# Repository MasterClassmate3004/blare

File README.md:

# Blare

## Description

Blare is a custom alarm clock with 6 keys, a buzzer and a TFT display. It has 2 modes, a stopwatch mode and a normal clock mode. A stopwatch mode measures elapsed time from the moment you start it to the moment you stop it. A normal clock time measures the normal time which you can adjust with the 2 specified buttons.

## Features
- 6 mechanical keys
- A buzzer
- TFT Display
- Dual mode (Stopwatch/Clock)
- Adjustable Time

## Bills of Materials
- 1x Seeed XIAO RP2040
- 6x MX-Style Switches
- 6x White Blank DSA keycaps
- 6x through hole 1N4148 Diodes
- 1x 2.25in TFT Screen
- 1x 3.3V Piezo Buzzer
- 1x 2.54mm 8pin Male Header
- 8x 20cm Female-Female Jumper Wires
- 8x M2X5X4 Heatset Inserts
- Top Case 3D Print
- Bottom Case 3D Print

## Images

# PCB

# CAD

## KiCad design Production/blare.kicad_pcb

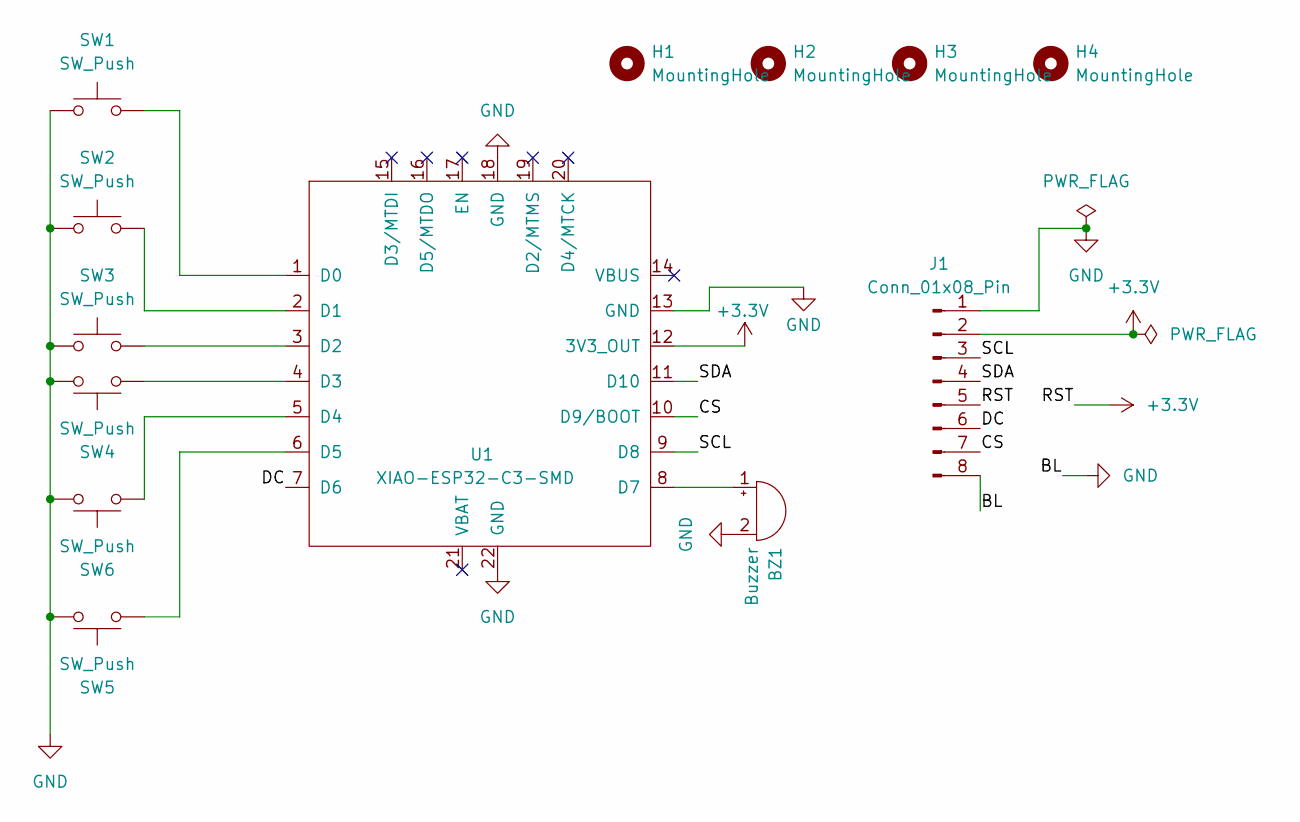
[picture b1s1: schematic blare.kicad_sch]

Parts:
BZ1: Buzzer; Buzzer_12x9.5RM7.6
H1, H2, H3, H4: MountingHole; MountingHole_3.2mm_M3
J1: Conn_01x08_Pin; PinSocket_1x08_P2.54mm_Vertical
SW1, SW2, SW3, SW4, SW5, SW6: SW_Push; SW_Cherry_MX_1.00u_PCB
U1: XIAO-ESP32-C3-SMD

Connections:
+3.3V: J1.2, J1.5, U1.12 (3V3_OUT)
/CS: J1.7, U1.10 (D9/BOOT)
/DC: J1.6, U1.7 (D6)
/SCL: J1.3, U1.9 (D8)
/SDA: J1.4, U1.11 (D10)
GND: BZ1.2 (-), J1.1, J1.8, SW1.1, SW2.1, SW3.1, SW4.2, SW5.2, SW6.2, U1.13 (GND), U1.18 (GND), U1.22 (GND)
unnamed: BZ1.1 (+), U1.8 (D7)
unnamed: SW1.2, U1.1 (D0)
unnamed: SW2.2, U1.2 (D1)
unnamed: SW3.2, U1.3 (D2)
unnamed: SW4.1, U1.4 (D3)
unnamed: SW6.1, U1.5 (D4)
unnamed: SW5.1, U1.6 (D5)

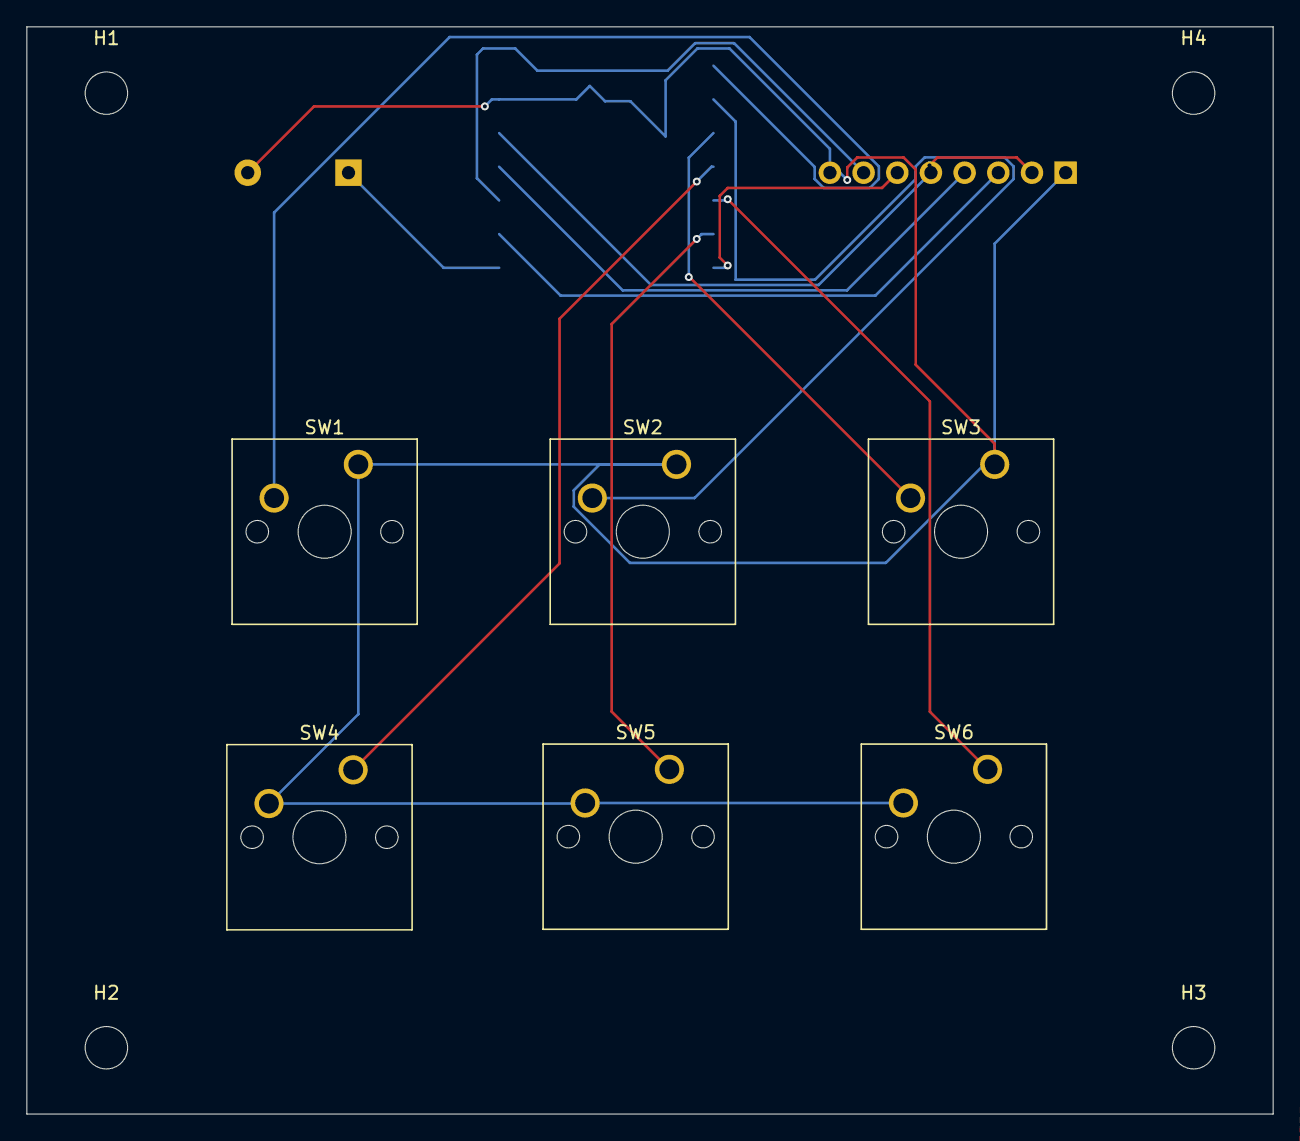
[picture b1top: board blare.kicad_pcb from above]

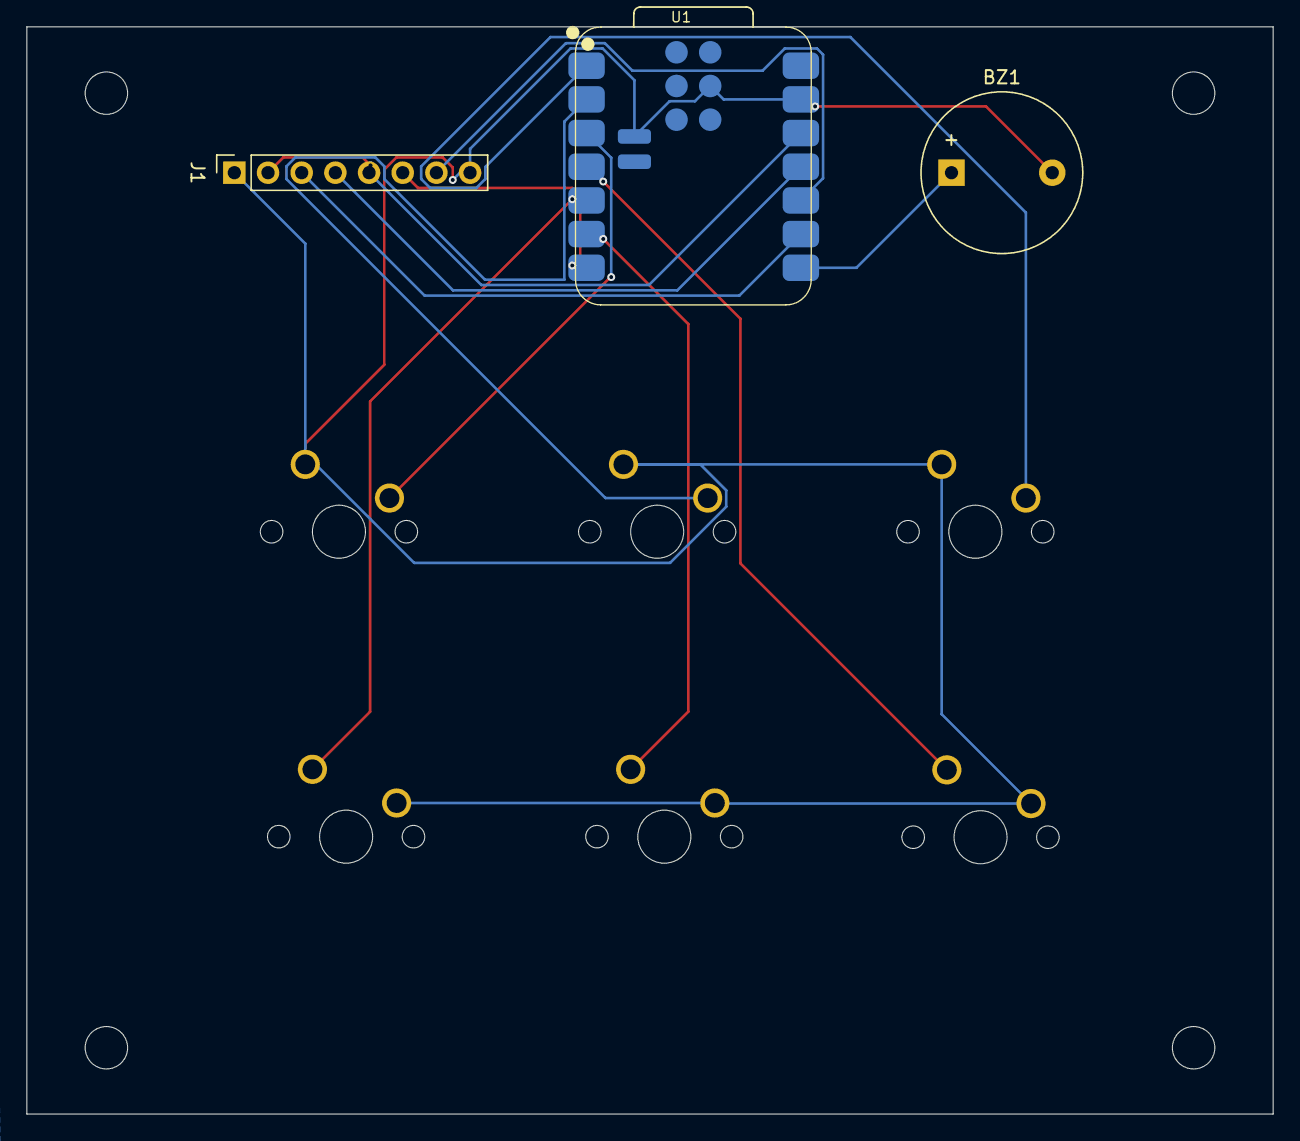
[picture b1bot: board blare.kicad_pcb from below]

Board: 2 copper layers, 94.0 x 82.0 mm, 13 parts (3 on the bottom side), 13 nets.
